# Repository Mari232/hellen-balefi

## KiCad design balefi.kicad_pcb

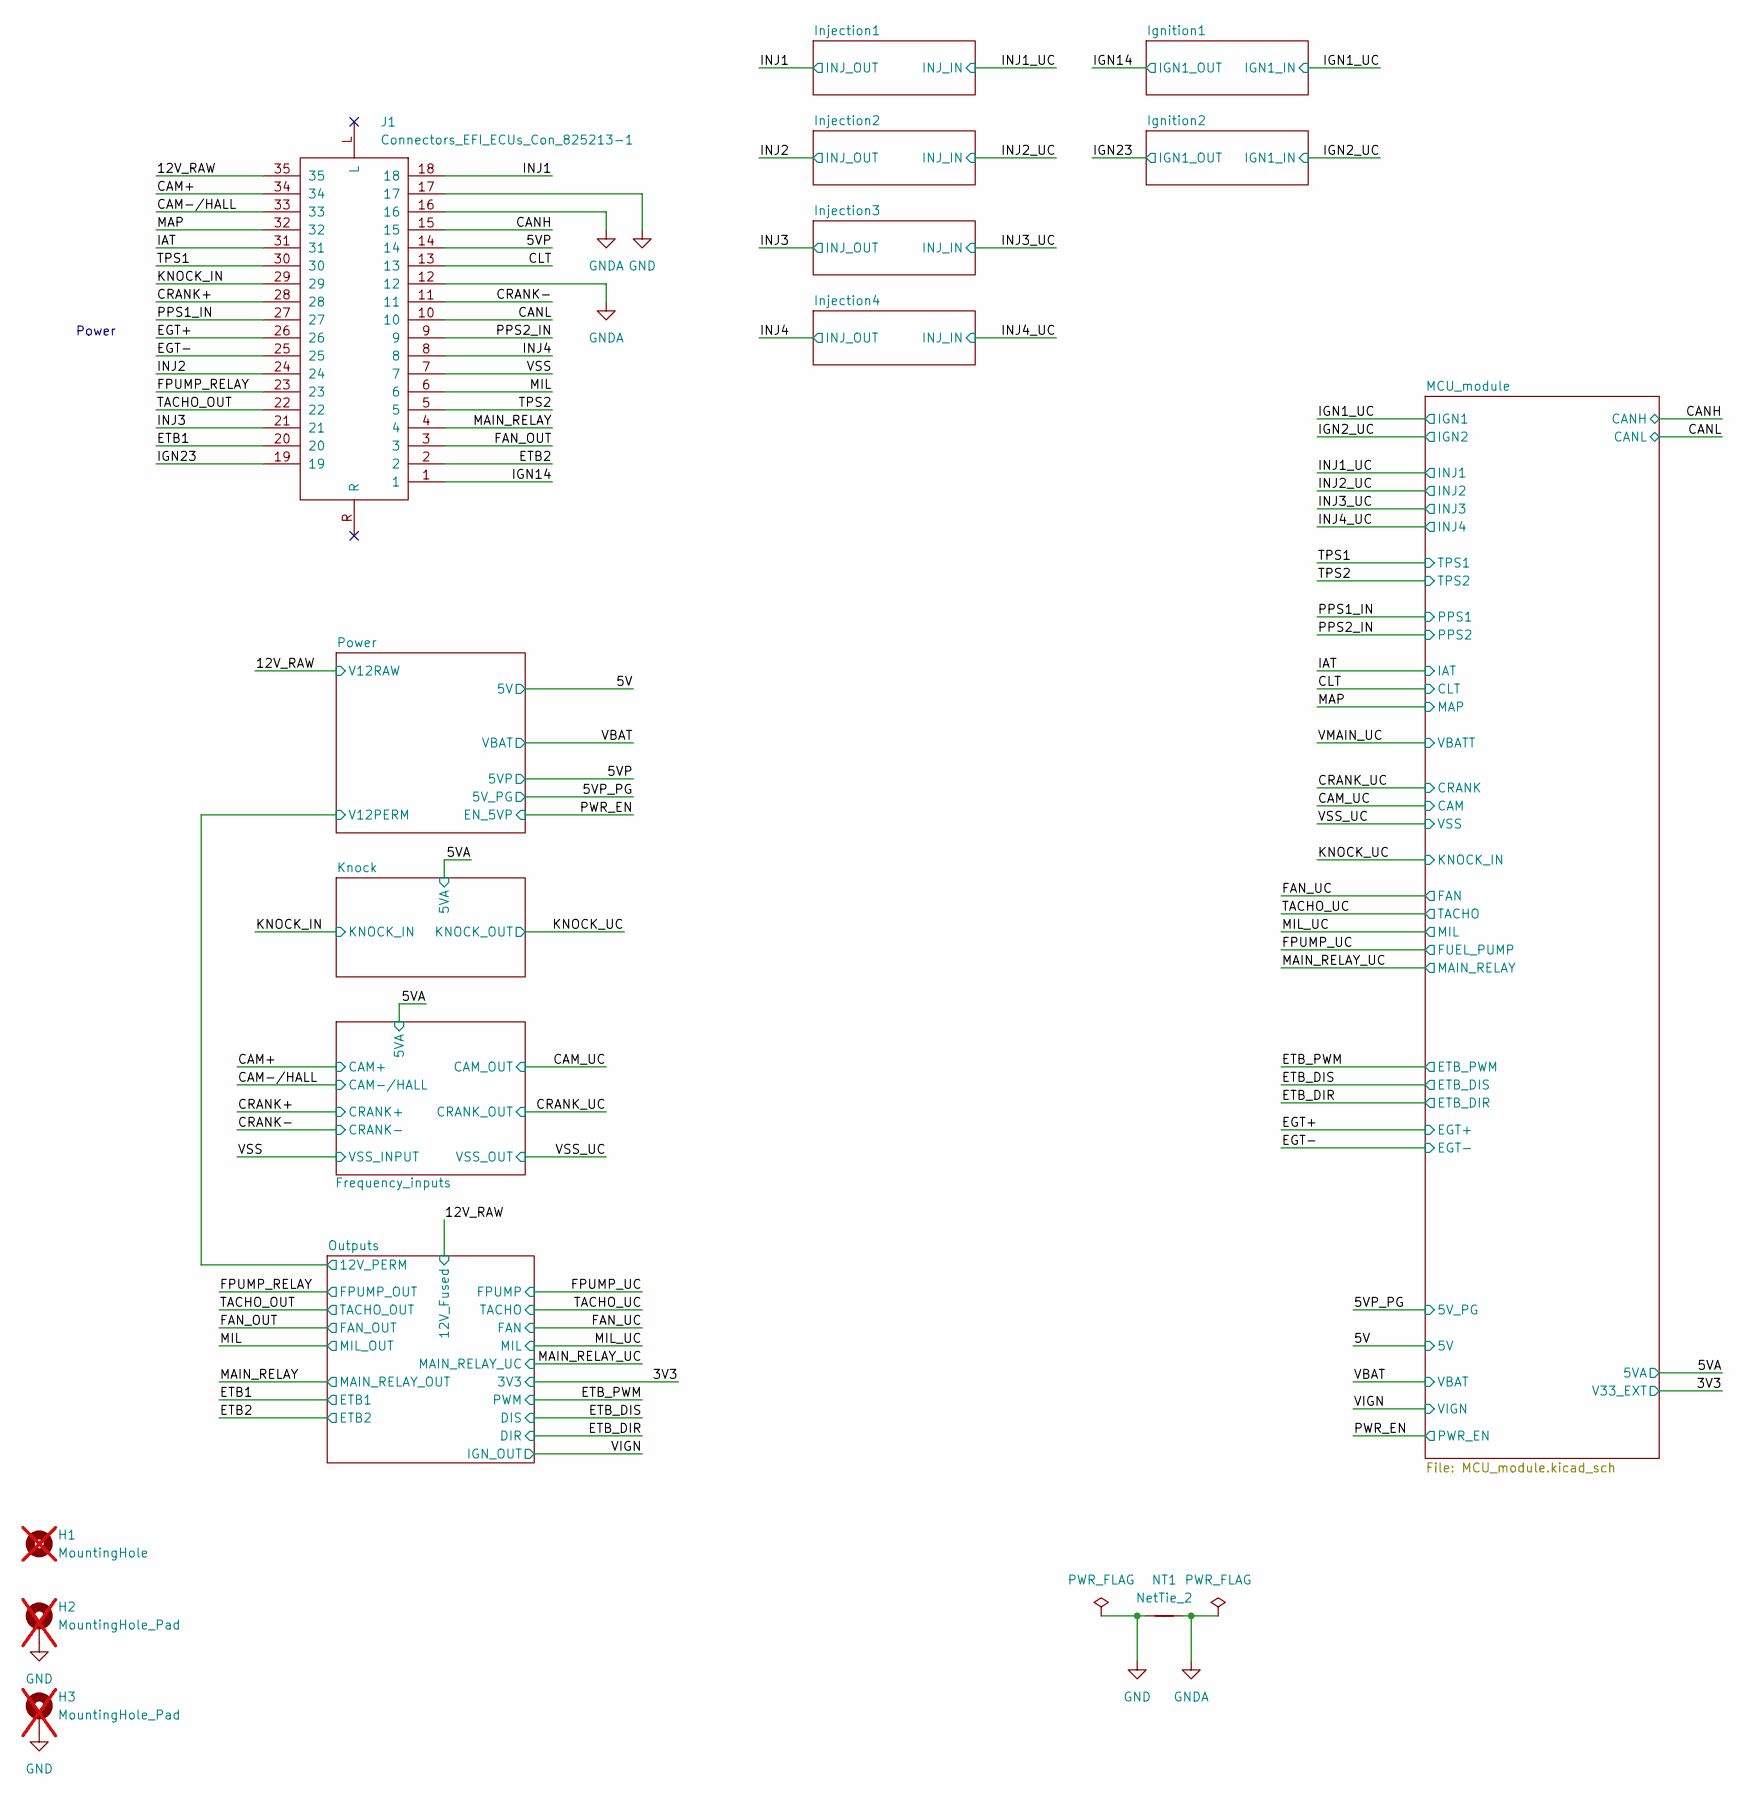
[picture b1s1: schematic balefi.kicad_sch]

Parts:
H1: MountingHole; MountingHole_3.7mm; not fitted
H2, H3: MountingHole_Pad; MountingHole_3.7mm_Pad_Via; not fitted
J1: Connectors_EFI_ECUs_Con_825213-1; 825213-1_FIAT
NT1: NetTie_2; NetTie-2_SMD_Pad2.0mm

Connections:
/5VP: J1.14; also elsewhere on the board
/12V_RAW: J1.35; also elsewhere on the board
/CAM+: J1.34; also elsewhere on the board
/CAM-/HALL: J1.33; also elsewhere on the board
/CANH: J1.15; also elsewhere on the board
/CANL: J1.10; also elsewhere on the board
/CLT: J1.13; also elsewhere on the board
/CRANK+: J1.28; also elsewhere on the board
/CRANK-: J1.11; also elsewhere on the board
/EGT+: J1.26; also elsewhere on the board
/EGT-: J1.25; also elsewhere on the board
/ETB1: J1.20; also elsewhere on the board
/ETB2: J1.2; also elsewhere on the board
/FAN_OUT: J1.3; also elsewhere on the board
/FPUMP_RELAY: J1.23; also elsewhere on the board
/IAT: J1.31; also elsewhere on the board
/IGN14: J1.1; also elsewhere on the board
/IGN23: J1.19; also elsewhere on the board
/INJ1: J1.18; also elsewhere on the board
/INJ2: J1.24; also elsewhere on the board
/INJ3: J1.21; also elsewhere on the board
/INJ4: J1.8; also elsewhere on the board
/KNOCK_IN: J1.29; also elsewhere on the board
/MAIN_RELAY: J1.4; also elsewhere on the board
/MAP: J1.32; also elsewhere on the board
/MIL: J1.6; also elsewhere on the board
/PPS1_IN: J1.27; also elsewhere on the board
/PPS2_IN: J1.9; also elsewhere on the board
/TACHO_OUT: J1.22; also elsewhere on the board
/TPS1: J1.30; also elsewhere on the board
/TPS2: J1.5; also elsewhere on the board
/VSS: J1.7; also elsewhere on the board
GND: H2.1, H3.1, J1.17, NT1.1; also elsewhere on the board
GNDA: J1.12, J1.16, NT1.2; also elsewhere on the board

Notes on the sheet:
Power

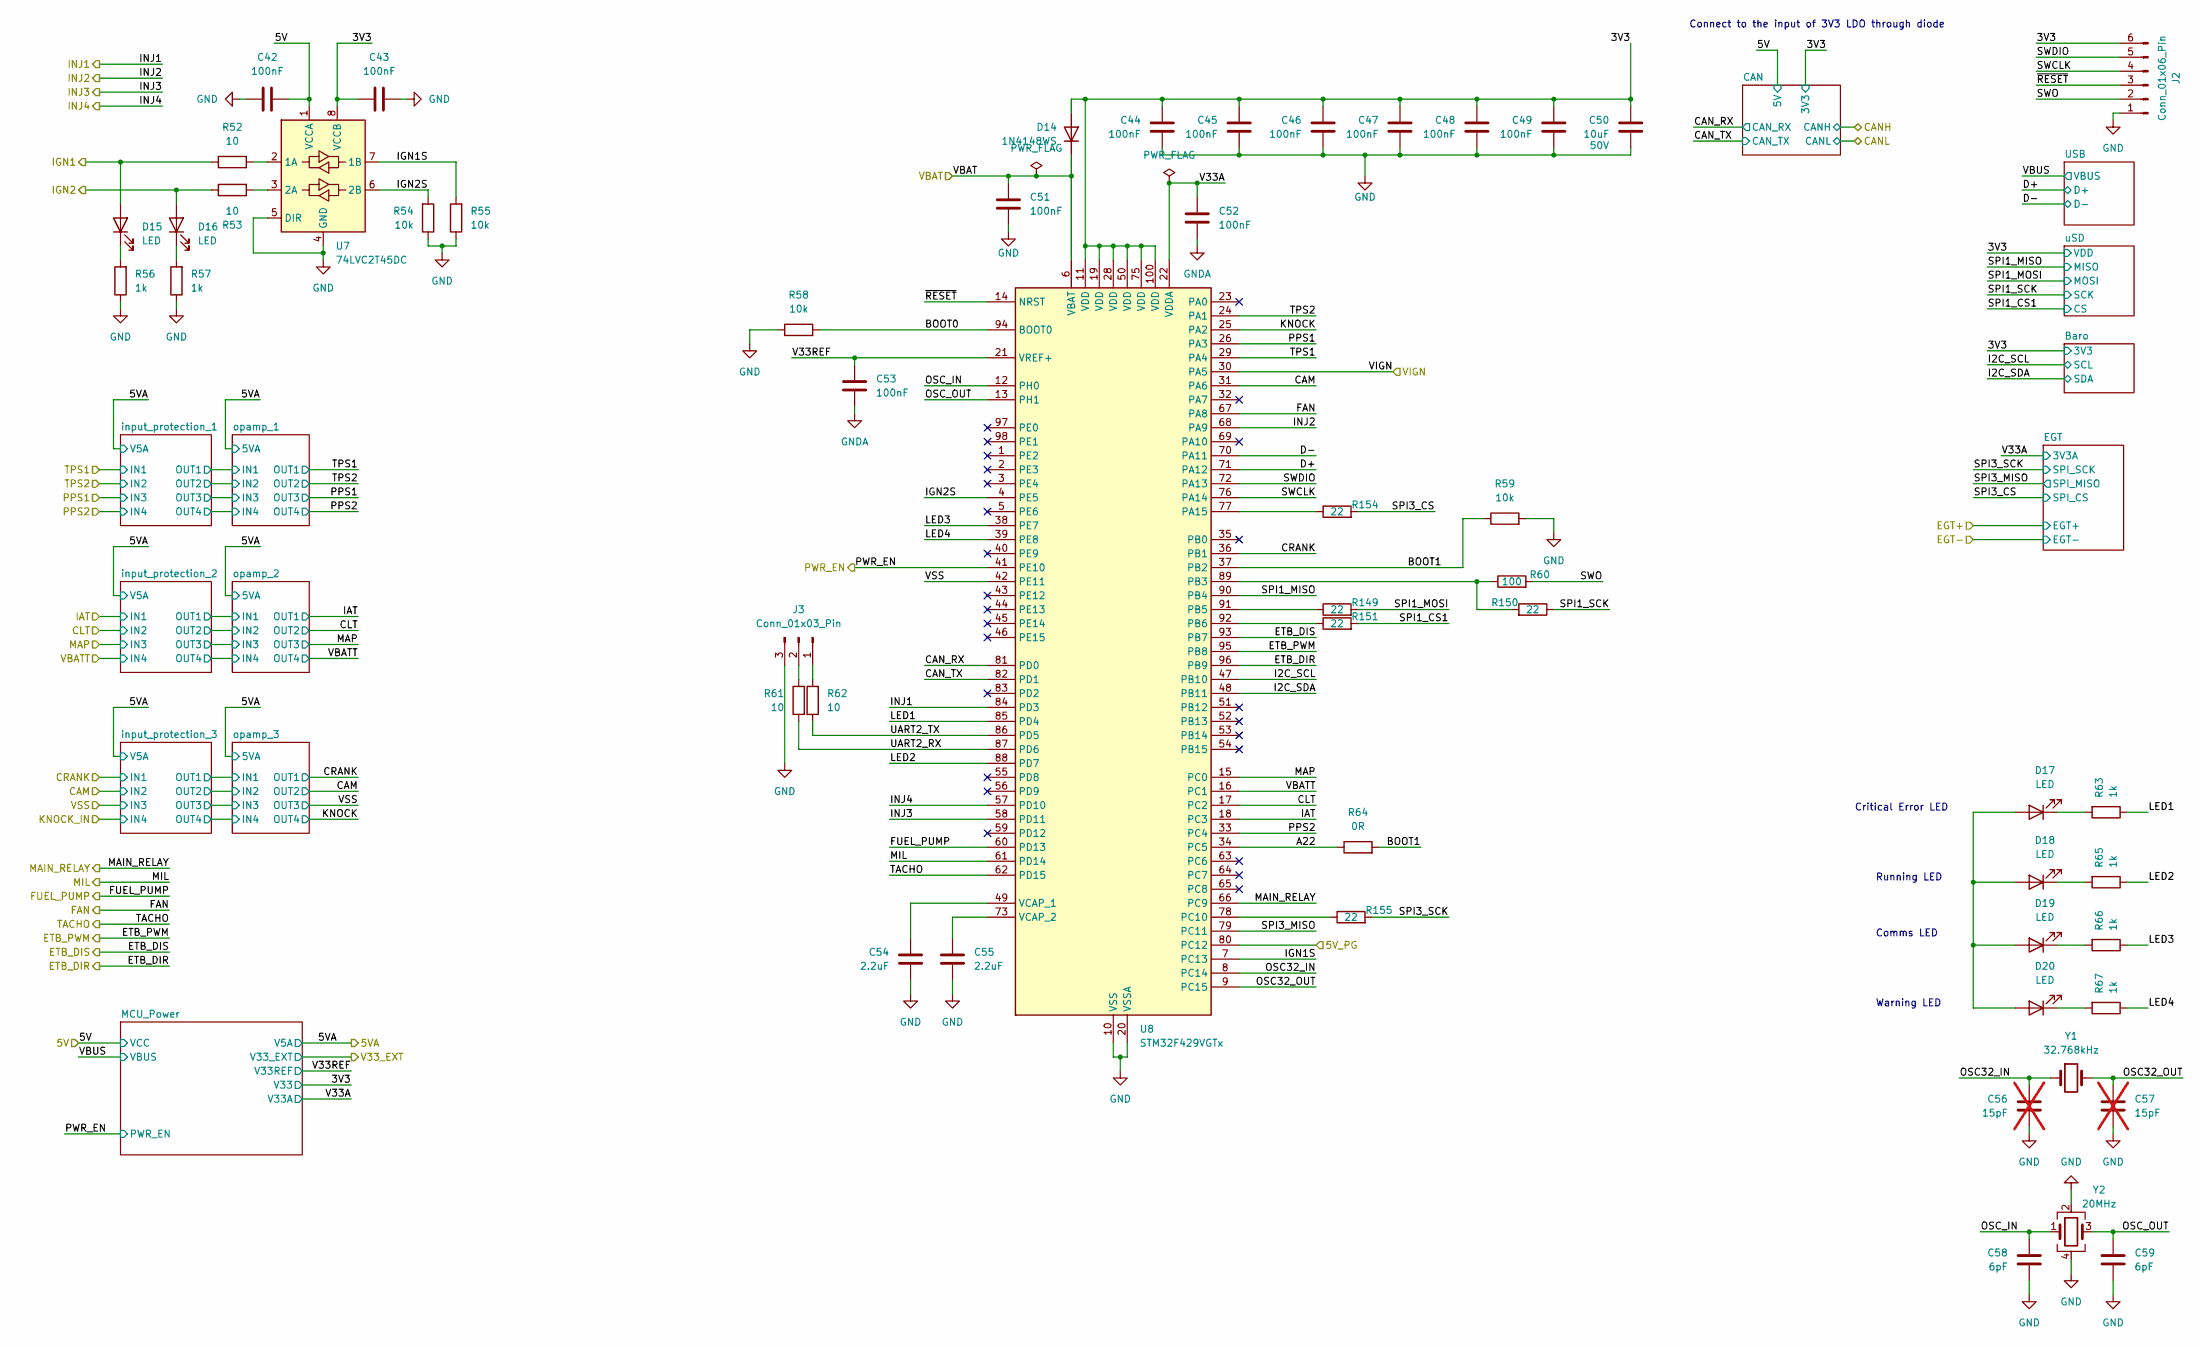
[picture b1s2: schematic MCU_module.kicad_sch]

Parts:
C42, C43, C44, C45, C46, C47, C48, C49, C51, C52, C53: 100nF; C_0402_1005Metric; MPN CL05B104KB54PNC
C50: 10uF; C_1206_3216Metric; MPN CL31A106KBHNNNE
C54, C55: 2.2uF; C_0805_2012Metric; MPN CL21B225KOFNNNE
C56, C57: 15pF; C_0402_1005Metric; MPN CGA2B2C0G1H150J050BD; not fitted
C58, C59: 6pF; C_0402_1005Metric; MPN GCM1555C1H6R0CA16J
D14: 1N4148WS; D_SOD-323; MPN 1N4148WS-7-F
D15, D16, D17, D18, D19, D20: LED; LED_0603_1608Metric; MPN 150060AS75000
J2: Conn_01x06_Pin; PinHeader_1x06_P2.54mm_Vertical
J3: Conn_01x03_Pin; PinHeader_1x03_P2.54mm_Vertical
R52, R53, R61, R62: 10; R_0402_1005Metric; MPN AC0402FR-0710RL
R54, R55, R58, R59: 10k; R_0402_1005Metric; MPN AC0402JR-0710KL
R56, R57, R63, R65, R66, R67: 1k; R_0402_1005Metric; MPN AC0402FR-071KL
R60: 100; R_0402_1005Metric; MPN AC0402FR-07100RL
R64: 0R; R_0402_1005Metric; MPN AC0402JR-070RL
R149, R150, R151, R154, R155: 22; R_0402_1005Metric; MPN AC0402FR-0722RL
U7: 74LVC2T45DC; VSSOP-8_2.3x2mm_P0.5mm; MPN 74LVC2T45DC-Q100H
U8: STM32F429VGTx; LQFP-100_14x14mm_P0.5mm; MPN STM32F429VGT6
Y1: 32.768kHz; Crystal_SMD_2012-2Pin_2.0x1.2mm; MPN ECS-.327-CDX-1082
Y2: 20MHz; Crystal_SMD_2520-4Pin_2.5x2.0mm; MPN ECS-200-8-36Q-AES-TR

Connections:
/5V: C42.2, U7.1 (VCCA); also elsewhere on the board
/5VP_PG: U8.80 (PC12); also elsewhere on the board
/CAM_UC: U8.31 (PA6); also elsewhere on the board
/CLT: U8.17 (PC2); also elsewhere on the board
/CRANK_UC: U8.36 (PB1); also elsewhere on the board
/ETB_DIR: U8.96 (PB9); also elsewhere on the board
/ETB_DIS: U8.93 (PB7); also elsewhere on the board
/ETB_PWM: U8.95 (PB8); also elsewhere on the board
/FAN_UC: U8.67 (PA8); also elsewhere on the board
/FPUMP_UC: U8.60 (PD13); also elsewhere on the board
/IAT: U8.18 (PC3); also elsewhere on the board
/IGN1_UC: D15.2 (A), R52.1; also elsewhere on the board
/IGN2_UC: D16.2 (A), R53.1; also elsewhere on the board
/INJ1_UC: U8.84 (PD3); also elsewhere on the board
/INJ2_UC: U8.68 (PA9); also elsewhere on the board
/INJ3_UC: U8.58 (PD11); also elsewhere on the board
/INJ4_UC: U8.57 (PD10); also elsewhere on the board
/MAIN_RELAY_UC: U8.66 (PC9); also elsewhere on the board
/MAP: U8.15 (PC0); also elsewhere on the board
/MCU_module/3V3: C43.1, C44.1, C45.1, C46.1, C47.1, C48.1, C49.1, C50.1, D14.2 (A), J2.6, U7.8 (VCCB), U8.11 (VDD), U8.19 (VDD), U8.28 (VDD), U8.50 (VDD), U8.75 (VDD), U8.100 (VDD); also elsewhere on the board
/MCU_module/A22: R64.1, U8.34 (PC5)
/MCU_module/BOOT0: R58.2, U8.94 (BOOT0)
/MCU_module/BOOT1: R59.1, R64.2, U8.37 (PB2)
/MCU_module/CAN_RX: U8.81 (PD0); also elsewhere on the board
/MCU_module/CAN_TX: U8.82 (PD1); also elsewhere on the board
/MCU_module/D+: U8.71 (PA12); also elsewhere on the board
/MCU_module/D-: U8.70 (PA11); also elsewhere on the board
/MCU_module/I2C_SCL: U8.47 (PB10); also elsewhere on the board
/MCU_module/I2C_SDA: U8.48 (PB11); also elsewhere on the board
/MCU_module/IGN1S: R55.2, U7.7 (1B), U8.7 (PC13)
/MCU_module/IGN2S: R54.2, U7.6 (2B), U8.4 (PE5)
/MCU_module/KNOCK: U8.25 (PA2); also elsewhere on the board
/MCU_module/LED1: R63.1, U8.85 (PD4)
/MCU_module/LED2: R65.1, U8.88 (PD7)
/MCU_module/LED3: R66.1, U8.38 (PE7)
/MCU_module/LED4: R67.1, U8.39 (PE8)
/MCU_module/OSC32_IN: C56.1, U8.8 (PC14), Y1.1
/MCU_module/OSC32_OUT: C57.1, U8.9 (PC15), Y1.2
/MCU_module/OSC_IN: C58.1, U8.12 (PH0), Y2.1
/MCU_module/OSC_OUT: C59.1, U8.13 (PH1), Y2.3
/MCU_module/SPI1_CS1: R151.2; also elsewhere on the board
/MCU_module/SPI1_MISO: U8.90 (PB4); also elsewhere on the board
/MCU_module/SPI1_MOSI: R149.2; also elsewhere on the board
/MCU_module/SPI1_SCK: R150.1; also elsewhere on the board
/MCU_module/SPI3_CS: R154.2; also elsewhere on the board
/MCU_module/SPI3_MISO: U8.79 (PC11); also elsewhere on the board
/MCU_module/SPI3_SCK: R155.2; also elsewhere on the board
/MCU_module/SWCLK: J2.4, U8.76 (PA14)
/MCU_module/SWDIO: J2.5, U8.72 (PA13)
/MCU_module/SWO: J2.2, R60.2
/MCU_module/UART2_RX: R61.2, U8.87 (PD6)
/MCU_module/UART2_TX: R62.1, U8.86 (PD5)
/MCU_module/V33A: C52.1, U8.22 (VDDA); also elsewhere on the board
/MCU_module/V33REF: C53.1, U8.21 (VREF+); also elsewhere on the board
/MCU_module/~RESET: J2.3, U8.14 (NRST)
/MIL_UC: U8.61 (PD14); also elsewhere on the board
/PPS1_IN: U8.26 (PA3); also elsewhere on the board
/PPS2_IN: U8.33 (PC4); also elsewhere on the board
/PWR_EN: U8.41 (PE10); also elsewhere on the board
/TACHO_UC: U8.62 (PD15); also elsewhere on the board
/TPS1: U8.29 (PA4); also elsewhere on the board
/TPS2: U8.24 (PA1); also elsewhere on the board
/VBAT: C51.1, D14.1 (K), U8.6 (VBAT); also elsewhere on the board
/VIGN: U8.30 (PA5); also elsewhere on the board
/VMAIN_UC: U8.16 (PC1); also elsewhere on the board
/VSS_UC: U8.42 (PE11); also elsewhere on the board
GND: C42.1, C43.2, C44.2, C45.2, C46.2, C47.2, C48.2, C49.2, C50.2, C51.2, C54.2, C55.2, C56.2, C57.2, C58.2, C59.2, J2.1, J3.3, R54.1, R55.1, R56.1, R57.1, R58.1, R59.2, U7.4 (GND), U7.5 (DIR), U8.10 (VSS), U8.20 (VSSA), U8.27 (VSS), U8.74 (VSS), U8.99 (VSS), Y2.2, Y2.4; also elsewhere on the board
GNDA: C52.2, C53.2; also elsewhere on the board
unnamed: D15.1 (K), R56.2
unnamed: D16.1 (K), R57.2
unnamed: D17.2 (A), D18.2 (A), D19.2 (A), D20.2 (A)
unnamed: D17.1 (K), R63.2
unnamed: D18.1 (K), R65.2
unnamed: D19.1 (K), R66.2
unnamed: D20.1 (K), R67.2
unnamed: J3.1, R62.2
unnamed: J3.2, R61.1
unnamed: R52.2, U7.2 (1A)
unnamed: R53.2, U7.3 (2A)
unnamed: R154.1, U8.77 (PA15)
unnamed: R60.1, R150.2, U8.89 (PB3)
unnamed: R149.1, U8.91 (PB5)
unnamed: R151.1, U8.92 (PB6)
unnamed: R155.1, U8.78 (PC10)
unnamed: C54.1, U8.49 (VCAP_1)
unnamed: C55.1, U8.73 (VCAP_2)

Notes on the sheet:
Connect to the input of 3V3 LDO through diode
Critical Error LED
Running LED
Warning LED
Comms LED

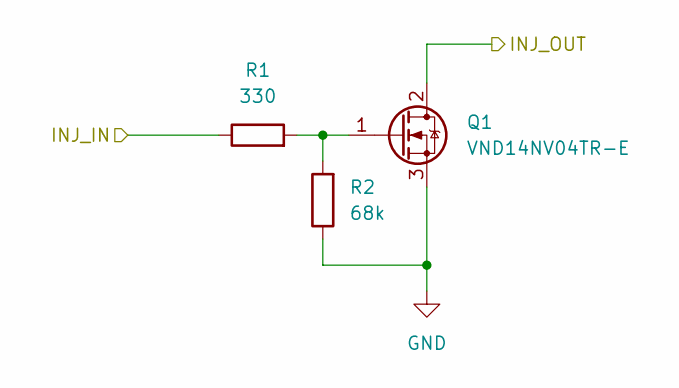
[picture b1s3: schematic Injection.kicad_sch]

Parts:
Q1: VND14NV04TR-E; TO-252-2; MPN VND14NV04TR-E
R1: 330; R_0402_1005Metric; MPN AC0402FR-07330RL
R2: 68k; R_0402_1005Metric; MPN AC0402FR-0768KL

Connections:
/INJ1: Q1.2 (D); also elsewhere on the board
/INJ1_UC: R1.1; also elsewhere on the board
GND: Q1.3 (S), R2.1; also elsewhere on the board
unnamed: Q1.1 (G), R1.2, R2.2

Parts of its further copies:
Q2, Q3, Q4: VND14NV04TR-E; TO-252-2; MPN VND14NV04TR-E
R3, R5, R7: 330; R_0402_1005Metric; MPN AC0402FR-07330RL
R4, R6, R8: 68k; R_0402_1005Metric; MPN AC0402FR-0768KL

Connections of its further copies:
/INJ2: Q2.2 (D); also elsewhere on the board
/INJ2_UC: R3.1; also elsewhere on the board
/INJ3: Q3.2 (D); also elsewhere on the board
/INJ3_UC: R5.1; also elsewhere on the board
/INJ4: Q4.2 (D); also elsewhere on the board
/INJ4_UC: R7.1; also elsewhere on the board
GND: Q2.3 (S), Q3.3 (S), Q4.3 (S), R4.1, R6.1, R8.1; also elsewhere on the board
unnamed: Q2.1 (G), R3.2, R4.2
unnamed: Q3.1 (G), R5.2, R6.2
unnamed: Q4.1 (G), R7.2, R8.2

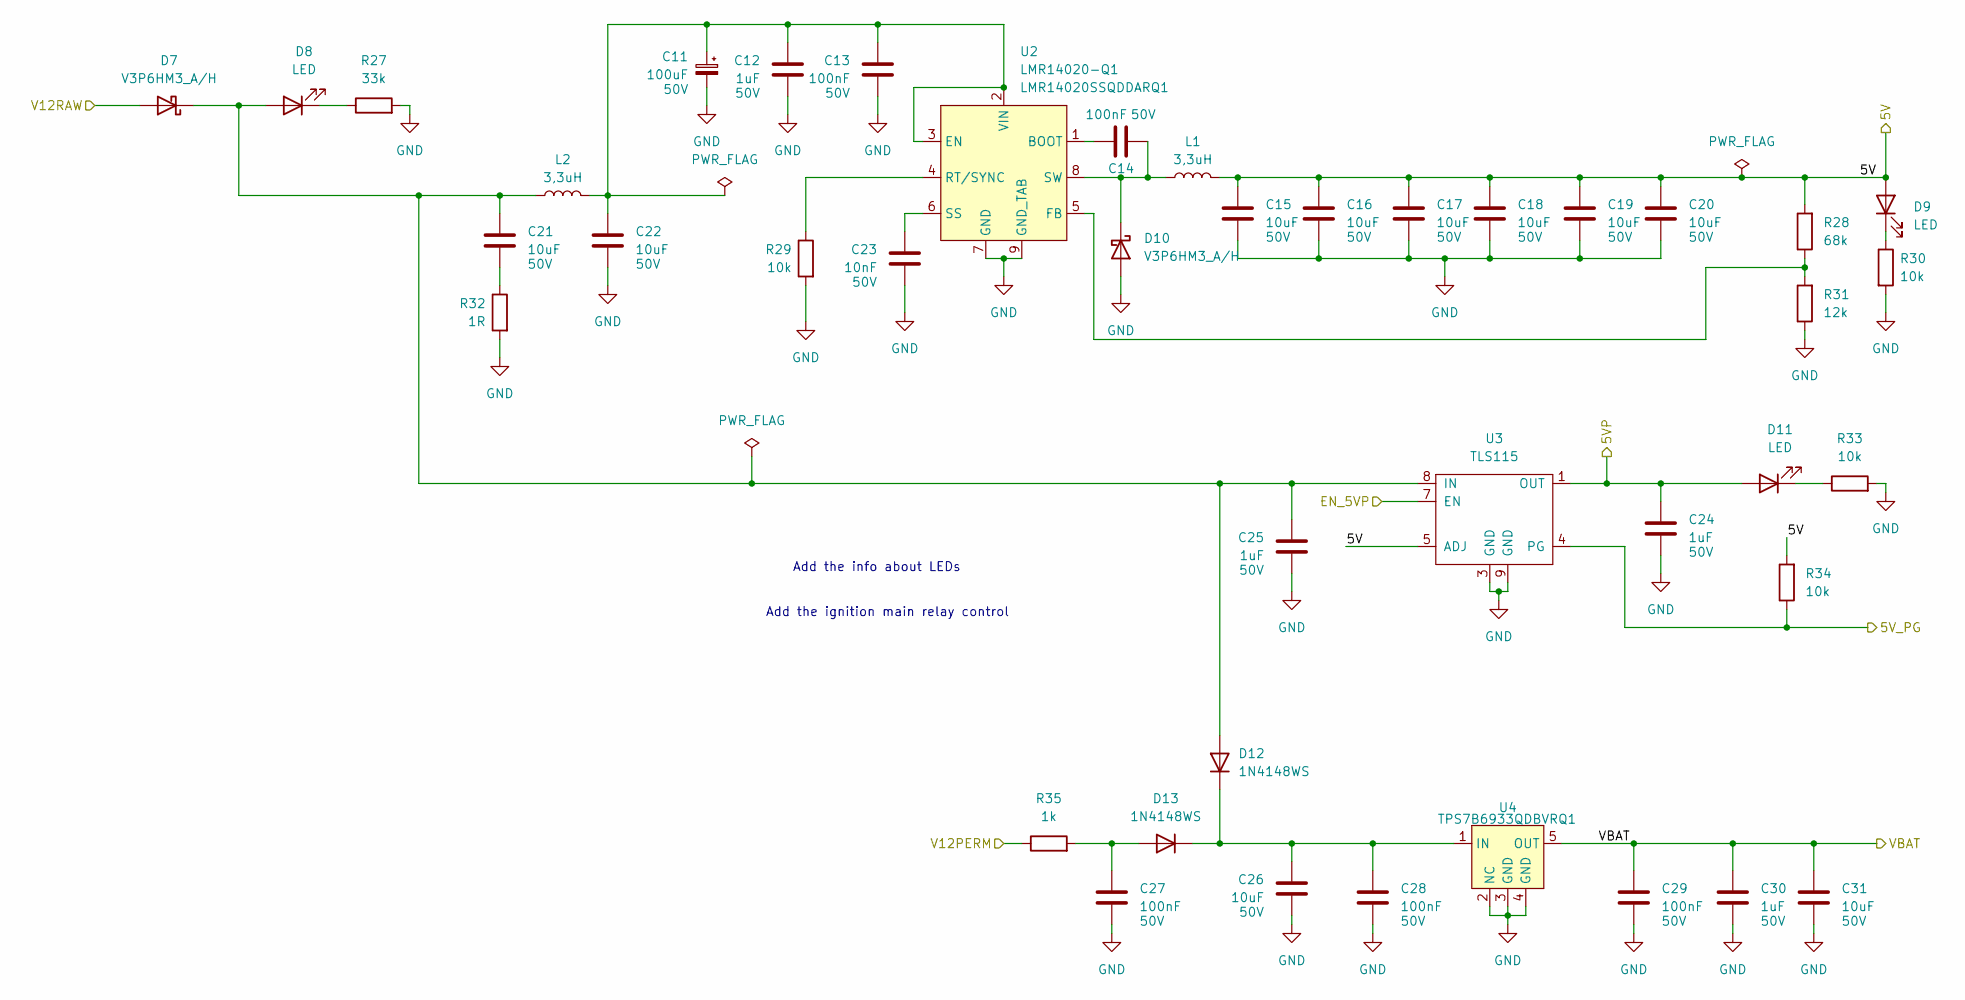
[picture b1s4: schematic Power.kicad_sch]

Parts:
C11: 100uF; CP_Elec_8x10; MPN UCD1H101MNL1GS
C12, C24, C25, C30: 1uF; C_0805_2012Metric; MPN CL21B105KBFNNNG
C13, C14, C27, C28, C29: 100nF; C_0402_1005Metric; MPN CL05B104KB54PNC
C15, C16, C17, C18, C19, C20, C21, C22, C26, C31: 10uF; C_1206_3216Metric; MPN CL31A106KBHNNNE
C23: 10nF; C_0402_1005Metric; MPN GCM155R71H103MA55D
D7, D10: V3P6HM3_A/H; Vishay_SMPA; MPN V3P6HM3_A/H
D8, D9, D11: LED; LED_0603_1608Metric; MPN 150060AS75000
D12, D13: 1N4148WS; D_SOD-323; MPN 1N4148WS-7-F
L1, L2: 3,3uH; L_TDK_VLS6045EX_VLS6045AF; MPN VLS6045EX-3R3N-H
R27: 33k; R_0402_1005Metric; MPN AC0402FR-0733KL
R28: 68k; R_0402_1005Metric; MPN AC0402FR-0768KL
R29, R30, R33, R34: 10k; R_0402_1005Metric; MPN AC0402JR-0710KL
R31: 12k; R_0402_1005Metric; MPN AC0402FR-0712KL
R32: 1R; R_0603_1608Metric; MPN AF0603FR-071RL
R35: 1k; R_0402_1005Metric; MPN AC0402FR-071KL
U2: LMR14020-Q1; Texas_R-PDSO-G8_EP2.95x4.9mm_Mask2.4x3.1mm_ThermalVias; MPN LMR14020SSQDDARQ1
U3: TLS115; Texas_R-PDSO-G8_EP2.95x4.9mm_Mask2.4x3.1mm_ThermalVias; MPN TLS115B0EJXUMA1
U4: TPS7B6933QDBVRQ1; SOT-23-5; MPN TPS7B6933QDBVRQ1

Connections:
/5V: C15.1, C16.1, C17.1, C18.1, C19.1, C20.1, D9.2 (A), L1.2, R28.2, R34.2, U3.5 (ADJ); also elsewhere on the board
/5VP: C24.1, D11.2 (A), U3.1 (OUT); also elsewhere on the board
/5VP_PG: R34.1, U3.4 (PG); also elsewhere on the board
/12V_RAW: D7.2 (A); also elsewhere on the board
/Outputs/12V_PERM: R35.1; also elsewhere on the board
/PWR_EN: U3.7 (EN); also elsewhere on the board
/VBAT: C29.1, C30.1, C31.1, U4.5 (OUT); also elsewhere on the board
GND: C11.2, C12.2, C13.2, C15.2, C16.2, C17.2, C18.2, C19.2, C20.2, C22.2, C23.2, C24.2, C25.2, C26.2, C27.2, C28.2, C29.2, C30.2, C31.2, D10.2 (A), R27.2, R29.2, R30.2, R31.1, R32.2, R33.2, U2.7 (GND), U2.9 (GND_TAB), U3.3 (GND), U3.9 (GND), U4.2 (NC), U4.3 (GND), U4.4 (GND); also elsewhere on the board
unnamed: C21.2, R32.1
unnamed: D8.1 (K), R27.1
unnamed: D9.1 (K), R30.1
unnamed: C14.1, D10.1 (K), L1.1, U2.8 (SW)
unnamed: D11.1 (K), R33.1
unnamed: C21.1, C25.1, D7.1 (K), D8.2 (A), D12.2 (A), L2.1, U3.8 (IN)
unnamed: C26.1, C28.1, D12.1 (K), D13.1 (K), U4.1 (IN)
unnamed: C27.1, D13.2 (A), R35.2
unnamed: C14.2, U2.1 (BOOT)
unnamed: C11.1, C12.1, C13.1, C22.1, L2.2, U2.2 (VIN), U2.3 (EN)
unnamed: R28.1, R31.2, U2.5 (FB)
unnamed: R29.1, U2.4 (RT/SYNC)
unnamed: C23.1, U2.6 (SS)

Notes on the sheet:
Add the info about LEDs
Add the ignition main relay control

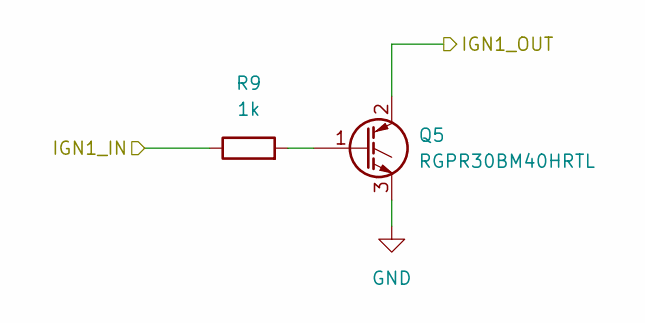
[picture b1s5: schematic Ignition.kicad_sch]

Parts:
Q5: RGPR30BM40HRTL; TO-252-2; MPN RGPR30BM40HRTL
R9: 1k; R_0402_1005Metric; MPN AC0402FR-071KL

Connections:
/IGN1_UC: R9.1; also elsewhere on the board
/IGN14: Q5.2 (C); also elsewhere on the board
GND: Q5.3 (E); also elsewhere on the board
unnamed: Q5.1 (G), R9.2

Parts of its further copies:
Q6: RGPR30BM40HRTL; TO-252-2; MPN RGPR30BM40HRTL
R10: 1k; R_0402_1005Metric; MPN AC0402FR-071KL

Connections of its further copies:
/IGN2_UC: R10.1; also elsewhere on the board
/IGN23: Q6.2 (C); also elsewhere on the board
GND: Q6.3 (E); also elsewhere on the board
unnamed: Q6.1 (G), R10.2

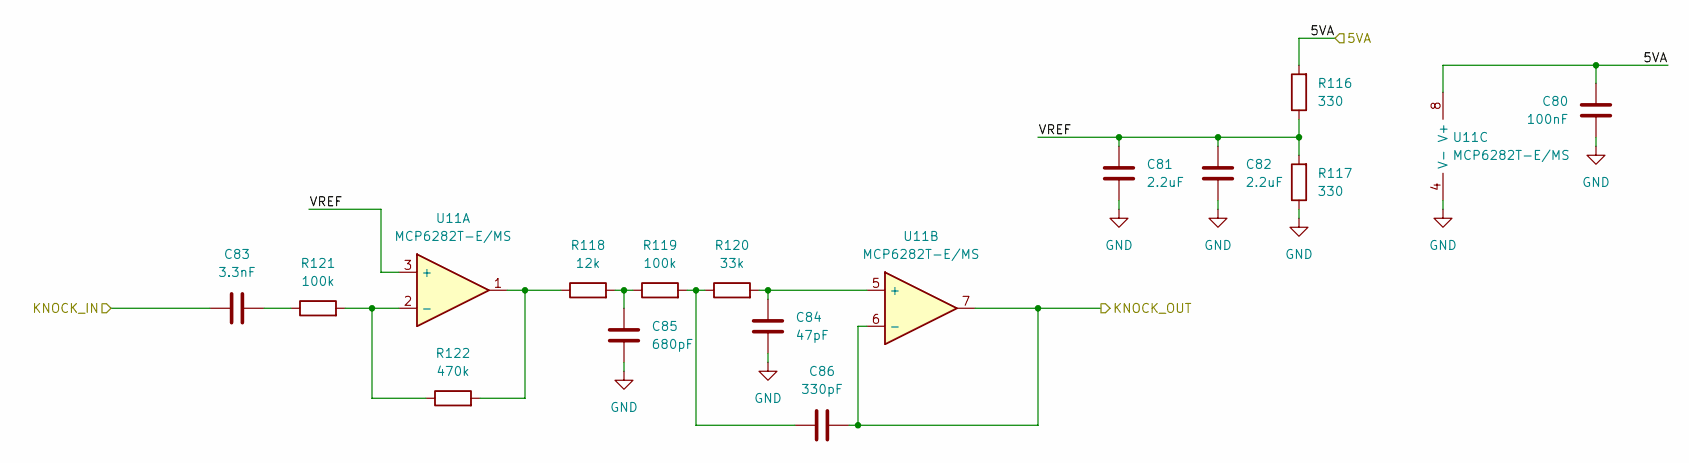
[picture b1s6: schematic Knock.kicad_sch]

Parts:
C80: 100nF; C_0402_1005Metric; MPN CL05B104KB54PNC
C81, C82: 2.2uF; C_0805_2012Metric; MPN CL21B225KOFNNNE
C83: 3.3nF; C_0402_1005Metric; MPN GCM155R71H332KA37D
C84: 47pF; C_0402_1005Metric; MPN CL05C470JB51PNC
C85: 680pF; C_0402_1005Metric; MPN GCM155R71H681KA37J
C86: 330pF; C_0402_1005Metric; MPN GCM155R71H331KA37D
R116, R117: 330; R_0402_1005Metric; MPN AC0402FR-07330RL
R118: 12k; R_0402_1005Metric; MPN AC0402FR-0712KL
R119, R121: 100k; R_0402_1005Metric; MPN AC0402FR-07100KL
R120: 33k; R_0402_1005Metric; MPN AC0402FR-0733KL
R122: 470k; R_0402_1005Metric
U11: MCP6282T-E/MS; MSOP-8_3x3mm_P0.65mm; MPN MCP6282T-E/MS

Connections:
/5VA: C80.1, R116.2, U11.8 (V+); also elsewhere on the board
/KNOCK_IN: C83.1; also elsewhere on the board
/KNOCK_UC: C86.1, U11.6 (-), U11.7; also elsewhere on the board
/Knock/VREF: C81.1, C82.1, R116.1, R117.2, U11.3 (+)
GND: C80.2, C81.2, C82.2, C84.1, C85.1, R117.1, U11.4 (V-); also elsewhere on the board
unnamed: C83.2, R121.1
unnamed: C85.2, R118.2, R119.1
unnamed: C86.2, R119.2, R120.1
unnamed: R118.1, R122.2, U11.1
unnamed: R121.2, R122.1, U11.2 (-)
unnamed: C84.2, R120.2, U11.5 (+)

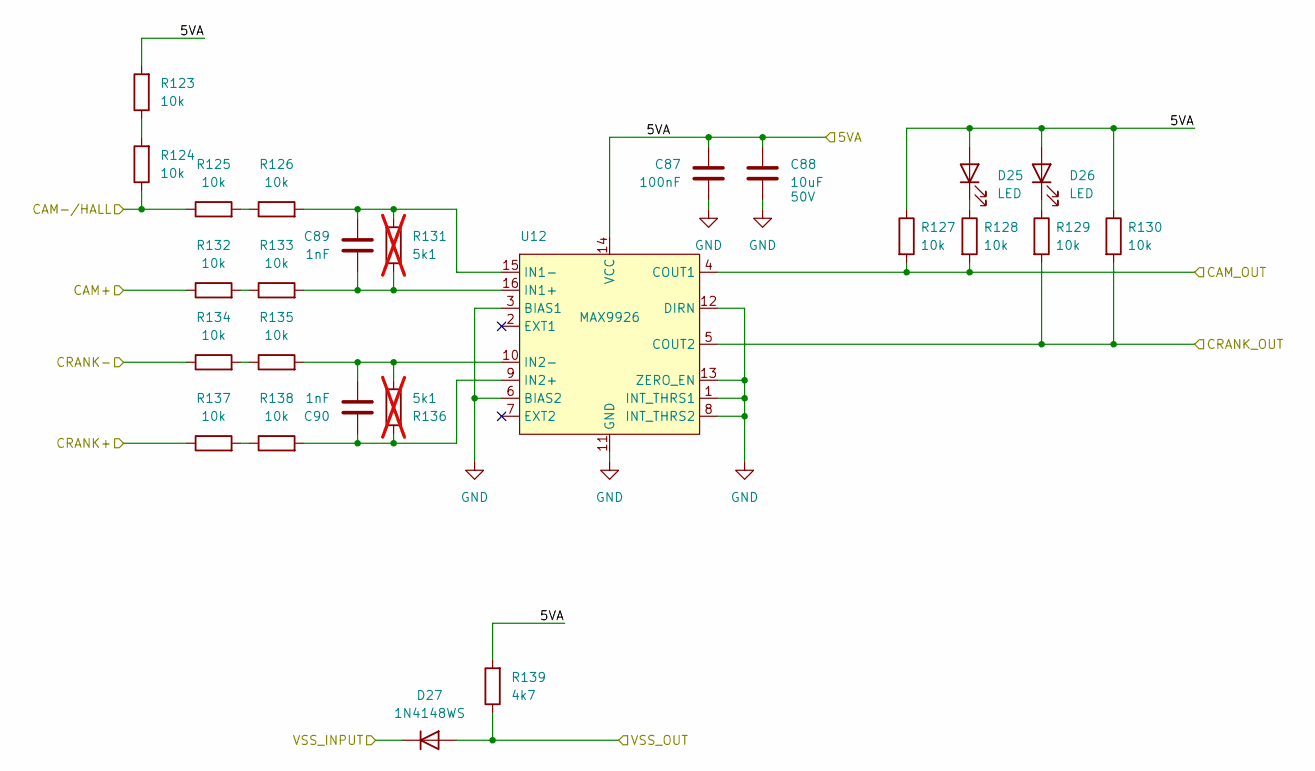
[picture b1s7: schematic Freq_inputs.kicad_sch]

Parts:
C87: 100nF; C_0402_1005Metric; MPN CL05B104KB54PNC
C88: 10uF; C_1206_3216Metric; MPN CL31A106KBHNNNE
C89, C90: 1nF; C_0805_2012Metric; MPN CL10B102KB8WPNC
D25, D26: LED; LED_0603_1608Metric; MPN 150060AS75000
D27: 1N4148WS; D_SOD-323; MPN 1N4148WS-7-F
R123, R124, R125, R126, R132, R133, R134, R135, R137, R138: 10k; R_1206_3216Metric; MPN AC1206JR-0710KL
R127, R128, R129, R130: 10k; R_0402_1005Metric; MPN AC0402JR-0710KL
R131, R136: 5k1; R_0603_1608Metric; not fitted
R139: 4k7; R_0402_1005Metric; MPN AC0402FR-074K7L
U12: MAX9926; QSOP-16_3.9x4.9mm_P0.635mm; MPN MAX9926UAEE+T

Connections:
/5VA: C87.1, C88.1, D25.2 (A), D26.2 (A), R123.2, R127.1, R130.1, R139.2, U12.14 (VCC); also elsewhere on the board
/CAM+: R132.1; also elsewhere on the board
/CAM-/HALL: R124.1, R125.1; also elsewhere on the board
/CAM_UC: R127.2, R128.2, U12.4 (COUT1); also elsewhere on the board
/CRANK+: R137.1; also elsewhere on the board
/CRANK-: R134.1; also elsewhere on the board
/CRANK_UC: R129.2, R130.2, U12.5 (COUT2); also elsewhere on the board
/VSS: D27.1 (K); also elsewhere on the board
/VSS_UC: D27.2 (A), R139.1; also elsewhere on the board
GND: C87.2, C88.2, U12.1 (INT_THRS1), U12.3 (BIAS1), U12.6 (BIAS2), U12.8 (INT_THRS2), U12.11 (GND), U12.12 (DIRN), U12.13 (ZERO_EN); also elsewhere on the board
unnamed: D25.1 (K), R128.1
unnamed: D26.1 (K), R129.1
unnamed: R123.1, R124.2
unnamed: R125.2, R126.1
unnamed: R132.2, R133.1
unnamed: R134.2, R135.1
unnamed: R137.2, R138.1
unnamed: C89.2, R131.1, R133.2, U12.16 (IN1+)
unnamed: C89.1, R126.2, R131.2, U12.15 (IN1-)
unnamed: C90.1, R136.2, R138.2, U12.9 (IN2+)
unnamed: C90.2, R135.2, R136.1, U12.10 (IN2-)

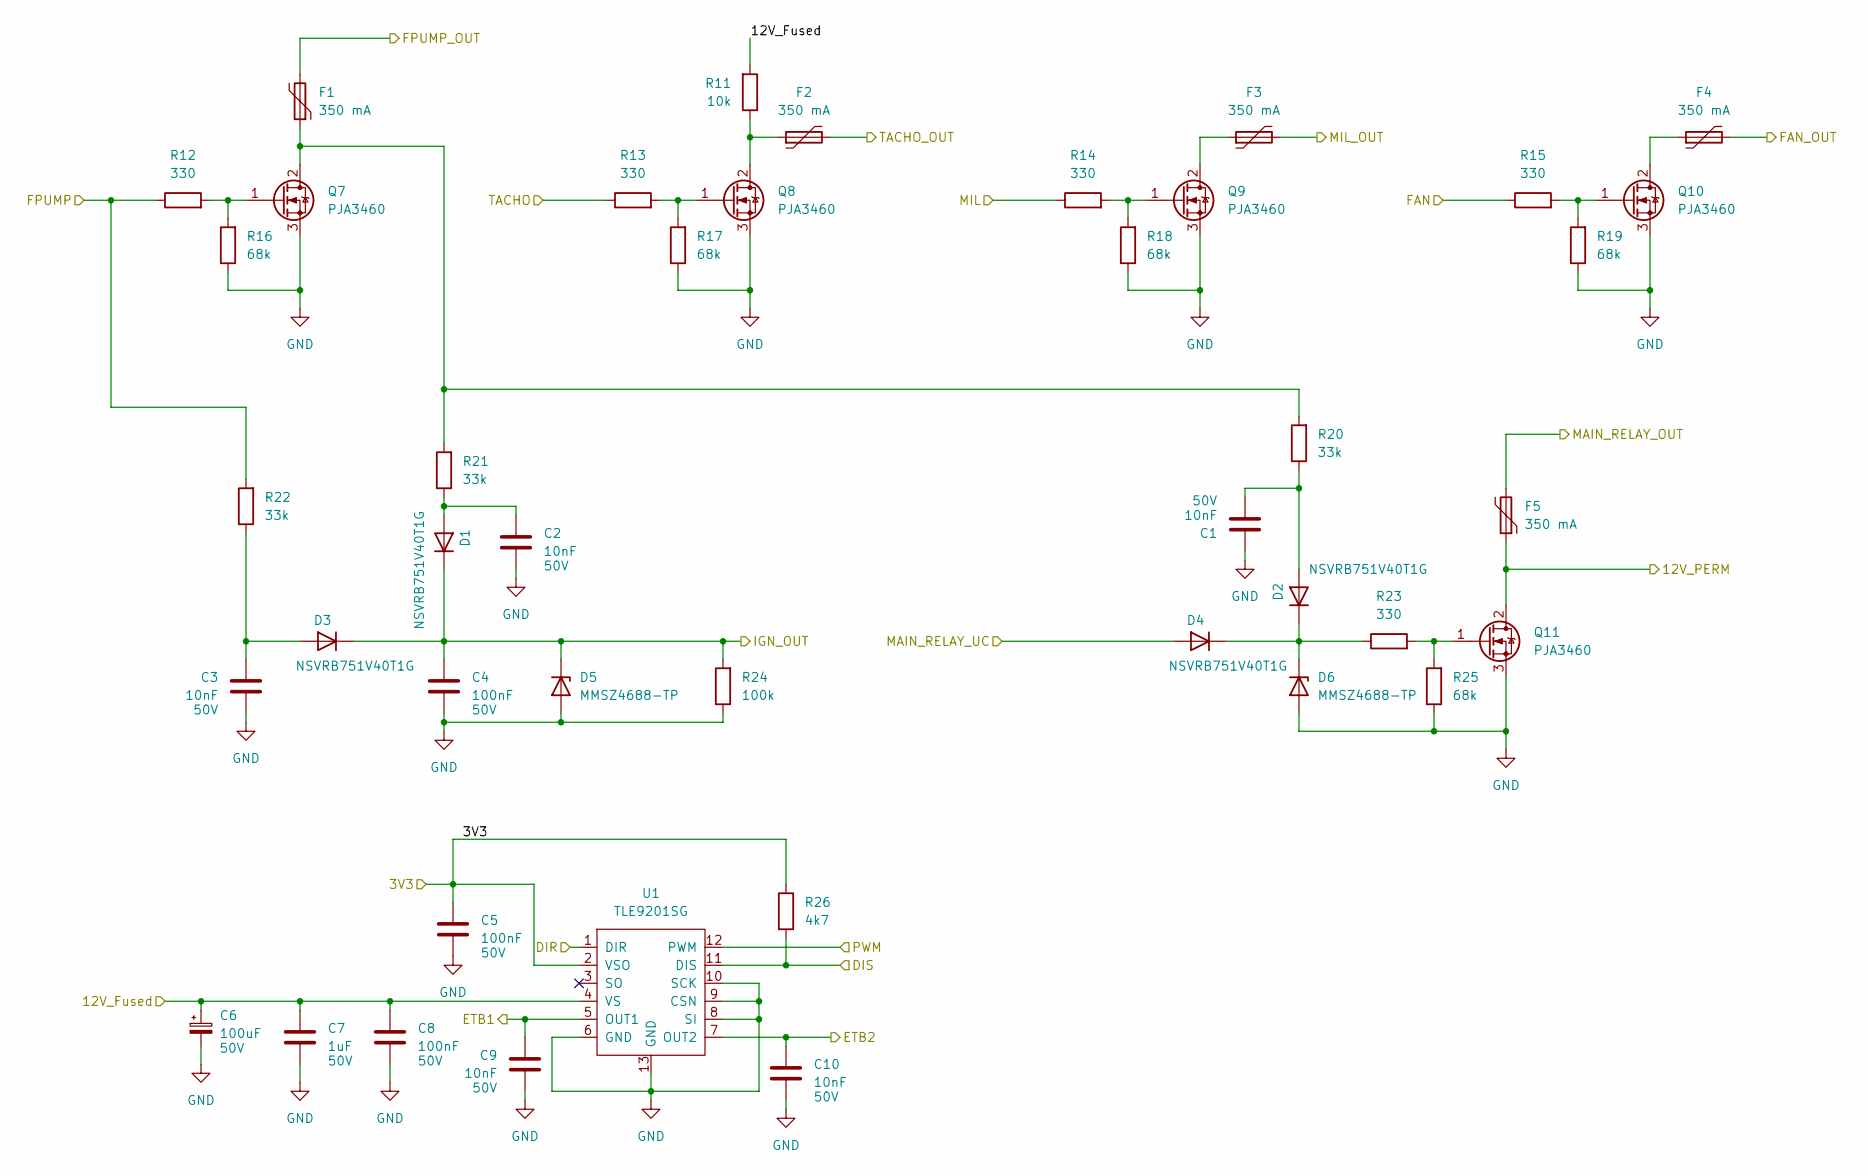
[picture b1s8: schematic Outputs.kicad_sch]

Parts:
C1, C2, C3, C9, C10: 10nF; C_0402_1005Metric; MPN GCM155R71H103MA55D
C4, C5, C8: 100nF; C_0402_1005Metric; MPN CL05B104KB54PNC
C6: 100uF; CP_Elec_8x10; MPN UCD1H101MNL1GS
C7: 1uF; C_0805_2012Metric; MPN CL21B105KBFNNNG
D1, D2, D3, D4: NSVRB751V40T1G; D_SOD-323; MPN NSVRB751V40T1G
D5, D6: MMSZ4688-TP; D_SOD-123; MPN MMSZ4688-TP
F1, F2, F3, F4, F5: 350 mA; Fuse_1206_3216Metric; MPN 0ZCJ0035FF2G
Q7, Q8, Q9, Q10, Q11: PJA3460; SOT-23-3; MPN PJA3460-AU_R1_000A1
R11: 10k; R_1206_3216Metric; MPN AC1206JR-0710KL
R12, R13, R14, R15, R23: 330; R_0402_1005Metric; MPN AC0402FR-07330RL
R16, R17, R18, R19, R25: 68k; R_0402_1005Metric; MPN AC0402FR-0768KL
R20, R21, R22: 33k; R_0402_1005Metric; MPN AC0402FR-0733KL
R24: 100k; R_0402_1005Metric; MPN AC0402FR-07100KL
R26: 4k7; R_0402_1005Metric; MPN AC0402FR-074K7L
U1: TLE9201SG; Infineon_PG-DSO-12-17_ThermalVias; MPN TLE9201SGAUMA1

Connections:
/3V3: C5.1, R26.1, U1.2 (VSO); also elsewhere on the board
/12V_RAW: C6.1, C7.1, C8.1, R11.2, U1.4 (VS); also elsewhere on the board
/ETB1: C9.1, U1.5 (OUT1); also elsewhere on the board
/ETB2: C10.1, U1.7 (OUT2); also elsewhere on the board
/ETB_DIR: U1.1 (DIR); also elsewhere on the board
/ETB_DIS: R26.2, U1.11 (DIS); also elsewhere on the board
/ETB_PWM: U1.12 (PWM); also elsewhere on the board
/FAN_OUT: F4.2; also elsewhere on the board
/FAN_UC: R15.1; also elsewhere on the board
/FPUMP_RELAY: F1.2; also elsewhere on the board
/FPUMP_UC: R12.1, R22.2; also elsewhere on the board
/MAIN_RELAY: F5.2; also elsewhere on the board
/MAIN_RELAY_UC: D4.2 (A); also elsewhere on the board
/MIL: F3.2; also elsewhere on the board
/MIL_UC: R14.1; also elsewhere on the board
/Outputs/12V_PERM: F5.1, Q11.2 (D); also elsewhere on the board
/TACHO_OUT: F2.2; also elsewhere on the board
/TACHO_UC: R13.1; also elsewhere on the board
/VIGN: C4.1, D1.1 (K), D3.1 (K), D5.1 (K), R24.2; also elsewhere on the board
GND: C1.1, C2.2, C3.2, C4.2, C5.2, C6.2, C7.2, C8.2, C9.2, C10.2, D5.2 (A), D6.2 (A), Q7.3 (S), Q8.3 (S), Q9.3 (S), Q10.3 (S), Q11.3 (S), R16.1, R17.1, R18.1, R19.1, R24.1, R25.1, U1.6 (GND), U1.8 (SI), U1.9 (CSN), U1.10 (SCK), U1.13 (GND); also elsewhere on the board
unnamed: C2.1, D1.2 (A), R21.1
unnamed: C1.2, D2.2 (A), R20.1
unnamed: D2.1 (K), D4.1 (K), D6.1 (K), R23.1
unnamed: C3.1, D3.2 (A), R22.1
unnamed: F1.1, Q7.2 (D), R20.2, R21.2
unnamed: Q7.1 (G), R12.2, R16.2
unnamed: F2.1, Q8.2 (D), R11.1
unnamed: Q8.1 (G), R13.2, R17.2
unnamed: F3.1, Q9.2 (D)
unnamed: Q9.1 (G), R14.2, R18.2
unnamed: F4.1, Q10.2 (D)
unnamed: Q10.1 (G), R15.2, R19.2
unnamed: Q11.1 (G), R23.2, R25.2
